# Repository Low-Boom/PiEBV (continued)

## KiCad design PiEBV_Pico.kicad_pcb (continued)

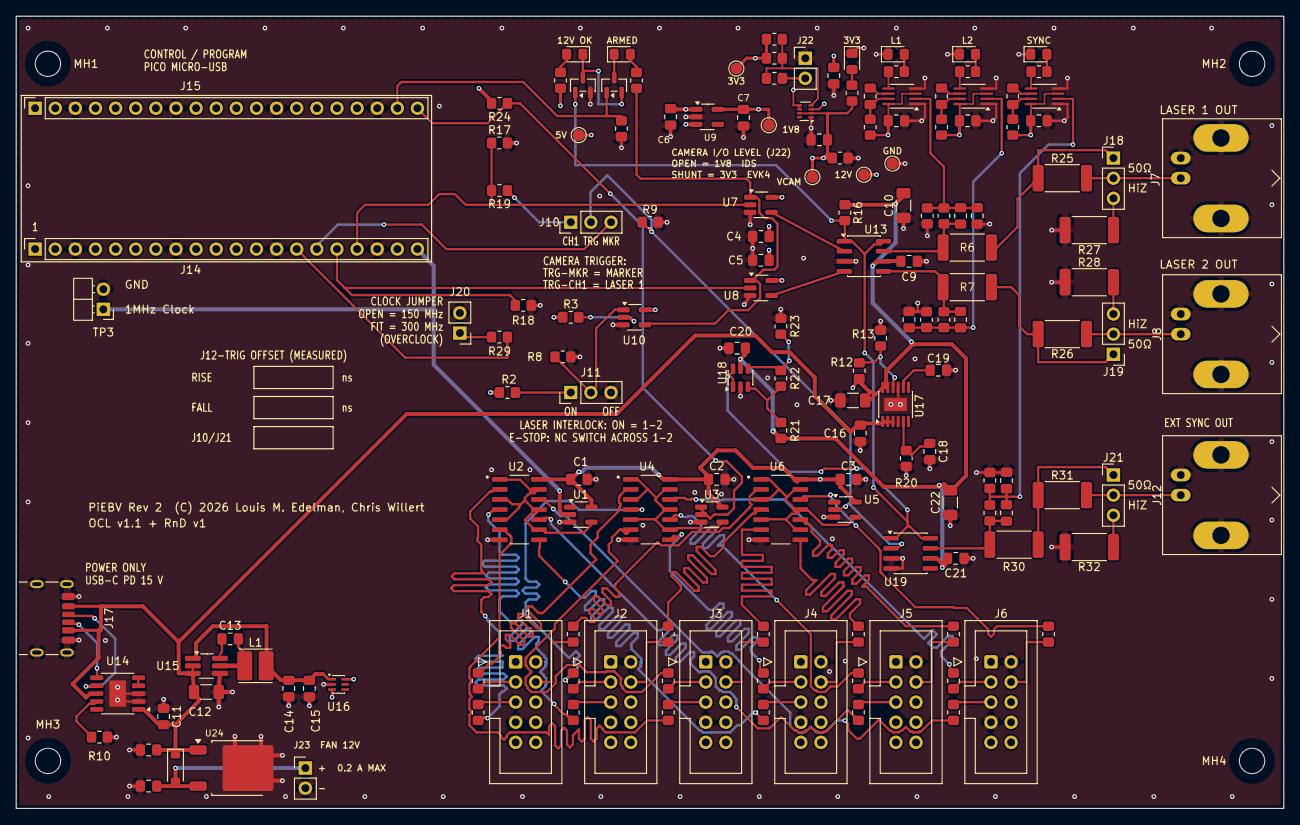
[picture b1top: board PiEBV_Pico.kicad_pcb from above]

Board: 4 copper layers, 160.0 x 100.0 mm, 164 parts (0 on the bottom side), 110 nets.

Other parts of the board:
MH1, MH2, MH3, MH4: MountingHole_3.2mm_M3

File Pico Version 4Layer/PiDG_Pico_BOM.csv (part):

"Reference","Value","Footprint","Qty","DNP","LCSC"
"C1-C5,C8,C9,C13,C20","0.1uF 50V X7R","Capacitor_SMD:C_0805_2012Metric_Pad1.18x1.45mm_HandSolder","9","","C49678"
"C6,C11,C16","1uF 50V X7R","Capacitor_SMD:C_0805_2012Metric_Pad1.18x1.45mm_HandSolder","3","","C28323"
"C7","2.2uF 16V X7R","Capacitor_SMD:C_0805_2012Metric_Pad1.18x1.45mm_HandSolder","1","","C28234"
"C10,C12,C17","10uF 50V X7R","Capacitor_SMD:C_1206_3216Metric_Pad1.33x1.80mm_HandSolder","3","","C89632"
"C14,C15","22uF 25V X5R","Capacitor_SMD:C_0805_2012Metric_Pad1.18x1.45mm_HandSolder","2","","C45783"
"C18","22nF 50V X7R","Capacitor_SMD:C_0805_2012Metric_Pad1.18x1.45mm_HandSolder","1","","C1729"
"C19","10nF 50V X7R","Capacitor_SMD:C_0805_2012Metric_Pad1.18x1.45mm_HandSolder","1","","C1710"
"L1","4.7uH, Isat >= 1.5 A","Inductor_SMD:L_Cenker_CKCS4030","1","","C354587"
"R2,R3,R5","3k3","Resistor_SMD:R_0805_2012Metric_Pad1.20x1.40mm_HandSolder","3","","C26010"
"R6,R7","68 1% 2W","Resistor_SMD:R_2512_6332Metric_Pad1.40x3.35mm_HandSolder","2","","C2793964"
"R25,R26","47 1% 2W (laser Hi-Z mode series)","Resistor_SMD:R_2512_6332Metric_Pad1.40x3.35mm_HandSolder","2","","C7209419"
"R27,R28","82 1% 2W (laser Hi-Z mode shunt)","Resistor_SMD:R_2512_6332Metric_Pad1.40x3.35mm_HandSolder","2","","C7468298"
"R8,R9,R17,R18,R24","10k","Resistor_SMD:R_0805_2012Metric_Pad1.20x1.40mm_HandSolder","5","","C17414"
"R10","56k","Resistor_SMD:R_0805_2012Metric_Pad1.20x1.40mm_HandSolder","1","","C17756"
"R12","100k 0.1%","Resistor_SMD:R_0805_2012Metric_Pad1.20x1.40mm_HandSolder","1","","C122537"
"R13","5.36k 0.1%","Resistor_SMD:R_0805_2012Metric_Pad1.20x1.40mm_HandSolder","1","","C706247"
"R16","100k","Resistor_SMD:R_0805_2012Metric_Pad1.20x1.40mm_HandSolder","1","","C149504"
"R19","100","Resistor_SMD:R_0805_2012Metric_Pad1.20x1.40mm_HandSolder","1","","C17408"
"R20","750 1%","Resistor_SMD:R_0805_2012Metric_Pad1.20x1.40mm_HandSolder","1","","C17818"
"R21","150k 1%","Resistor_SMD:R_0805_2012Metric_Pad1.20x1.40mm_HandSolder","1","","C17470"
"R22","1.2k 1%","Resistor_SMD:R_0805_2012Metric_Pad1.20x1.40mm_HandSolder","1","","C17379"
"R23","4.7k 1%","Resistor_SMD:R_0805_2012Metric_Pad1.20x1.40mm_HandSolder","1","","C17673"
"U1,U5","74LVC1G04","Package_TO_SOT_SMD:SOT-23-5_HandSoldering","2","","C7827"
"U3","74LVC1G00 (SN74LVC1G00DBVR, pixel-reset NAND)","Package_TO_SOT_SMD:SOT-23-5_HandSoldering","1","","C7826"
"U2,U4,U6","SN74LVC04AD","SN74LVC04AD:SOIC127P600X175-14N","3","","C485074"
"U7,U8,U10","74AHCT1G08","Package_TO_SOT_SMD:SOT-23-5_HandSoldering","3","","C113521"
"U9","NCP718xSN180","Package_TO_SOT_SMD:SOT-23-5_HandSoldering","1","","C892792"
"U12","74LVC1G17","Package_TO_SOT_SMD:SOT-23-5_HandSoldering","1","","C7836"
"U13","UCC27524","Package_SO:SOIC-8_3.9x4.9mm_P1.27mm","1","","C465729"
"U14","CH224A","Package_SO:SSOP-10-1EP_3.9x4.9mm_P1mm_EP2.1x3.3mm","1","","C42459160"
"U15","AP63205WU","Package_TO_SOT_SMD:TSOT-23-6_HandSoldering","1","","C2071056"
"U16","LM66100DCK","Package_TO_SOT_SMD:SOT-363_SC-70-6","1","","C2869734"
"U17","LT3065EDD#TRPBF (Analog Devices, adjustable)","Package_DFN_QFN:DFN-10-1EP_3x3mm_P0.5mm_EP1.65x2.38mm","1","","C670143"
"U18","TPS3700DDCR","Package_TO_SOT_SMD:SOT-23-6","1","","C33002"
"J1-J6","Conn_02x05_Odd_Even","Connector_IDC:IDC-Header_2x05_P2.54mm_Vertical","6","","C5665"
"J7,J8,J12","BNC 50R Kinghelm KH-BNC50-3511 (Laser 1 / Laser 2 / Pixel Reset)","PiDG_Local:BNC_Kinghelm_KH-BNC50-3511_Horizontal","3","","C2837587"
"J10,J11,J18,J19","Header 1x03 (J10 trigger select / J11 laser enable / J18, J19 laser output mode)","Connector_PinHeader_2.54mm:PinHeader_1x03_P2.54mm_Vertical","4","","C49257"
"(loose)","Jumper shunt, 2.54 mm 2-pin","-","4","Not placed on the board - fit J10 on 2-3, J11 on 1-2 (lasers enabled), J18 and J19 on 1-2 (50 ohm outputs) by hand","C100114"
"J16","Header 1x03 right-angle (EN/TRIG/GND)","PiDG_Local:PinHeader_1x03_P2.54mm_Horizontal_EdgeTrim","1","","C32713262"
"J17","USB-C receptacle 16P (HRO TYPE-C-31-M-12)","PiDG_Local:USB_C_Receptacle_HRO_TYPE-C-31-M-12_EdgeTrim","1","","C165948"
"TP3","Header 1x02 right-angle (1MHz sync + GND)","PiDG_Local:PinHeader_1x02_P2.54mm_Horizontal_EdgeTrim","1","","C32713261"
"TP4","Header 1x02 (CH2 monitor + GND)","Connector_PinHeader_2.54mm:PinHeader_1x02_P2.54mm_Vertical","1","","C32713268"
"J14,J15","Pico Socket A/B","Connector_PinSocket_2.54mm:PinSocket_1x20_P2.54mm_Vertical","2","","C2905423"
"U11","Raspberry Pi Pico 2 W","(no PCB footprint - plugs into J14/J15)","1","DNP - socket-mounted, do not place; source module separately",""
"MH1-MH4","M3 mounting hole","MountingHole:MountingHole_3.2mm_M3","4","Mechanical only - NPTH, nothing to place",""
"","","","","",""
"NOTE","U9 must be the FIXED 1.8 V NCP718 (NCP718xSN180, e.g. NCP718BSN180T1G or NCP718ASN180T1G)","Sets the camera I/O level. The IDS UE-39B0XCP-E I/O pins are 1.8 V sensor-level; do not substitute a 1.65 V, 1.7 V or 3.3 V option.","","",""
"NOTE","C6 is on +5V, C7 on +1V8 - use X7R, C6 rated >= 10 V","NCP718 needs >= 1 uF ceramic on its output for stability; C7 = 2.2 uF gives margin after DC-bias derating.","","",""
"NOTE","U12 must be a Schmitt-trigger part (74LVC1G17)","Gives the Pixel Reset BNC TTL-compatible thresholds and 0.5-0.8 V of hysteresis at 3.3 V. A plain 74LVC1G08/1G34 is not a substitute.","","",""
"NOTE","J16/TP3/J17 use PiDG_Local *_EdgeTrim footprint variants","Identical part and pad geometry to the stock footprints; only the silkscreen is clipped where the connector reaches the board edge. Order the standard parts.","","",""
"NOTE","R8 is a fail-safe interlock pull-down","Holds U10 pin 1 low when no jumper is fitted on J11, so the lasers default to DISABLED. R2 (3k3) still wins when the J11 1-2 jumper is fitted.","","",""
"NOTE","R9 is the J10 trigger-select pull-down","Holds PWM_TRIG_TAP (U5 input) low when no shunt is fitted on J10, so all six camera trigger lines idle low instead of floating.","","",""
"NOTE","U7/U8/U10 must be AHCT (TTL-input) parts, not LVC","At VCC = 5 V an LVC input needs 0.7 x VCC = 3.5 V to read high; the Pico drives these from 3.3 V GPIOs. AHCT reads high above 2.0 V.","","",""
"NOTE","R10 = 56k sets the USB PD request to 15 V","CH224A CFG1 table (datasheet Table 5-1): 6k8 = 9 V, 24k = 12 V, 56k = 15 V, 120k = 20 V, 210k = 28 V. Do not leave R10 off - an open CFG1 is outside the table. The laser outputs need a charger that offers 15 V (any USB-PD charger rated over 27 W).","","",""
"NOTE","U14 must be the CH224A (not the CH224K)","CH224A pin 1 (VHV) and pin 8 (VBUS) connect directly to VBUS_PD by copper, as the WCH CH224K-to-CH224A guide (datasheet 7.2.1) requires; R11/R15 of the CH224K design were removed. Do not fit a CH224K: it is discontinued, and its pin 1 is a 3.6 V VDD pin that VBUS_PD would destroy.","","",""
"NOTE","R12/R13 must be 0.1 % parts; R6/R7 1 %","They set the 11.8 V laser-driver rail and hence the LDP-V trigger amplitude (4.54-5.14 V into 50 ohm with U13 ROH 0-8.5 ohm, window 4.5-5.2 V). With 1 % divider resistors the worst-case corners fall outside the window.","","",""
"NOTE","U17 must be the ADJUSTABLE LT3065 (LT3065EDD), not a fixed LT3065-x","R12/R13 (100k/5.36k) set 11.8 V from the 600 mV ADJ reference. R20 (750 ohm) sets a 400 mA current limit and C18 (22 nF) on IMAX is required by the datasheet. Solder the exposed pad (two GND vias under it).","","",""
"NOTE","C9, C10, C17 see 12 V; C11, C12, C16 see up to 20 V","Use >= 25 V parts for C9/C10/C17 and >= 50 V for C11/C12/C16 (X7R). C12 is the only large cap on VBUS_PD (C11 and C16 are 1 uF each): keep total VBUS capacitance near the USB-C 10 uF sink limit.","","",""
"NOTE","U16 CE is tied to its VOUT (+5V)","That is TI's always-on reverse-blocking connection. With CE grounded the LM66100 does NOT block reverse current.","","",""
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
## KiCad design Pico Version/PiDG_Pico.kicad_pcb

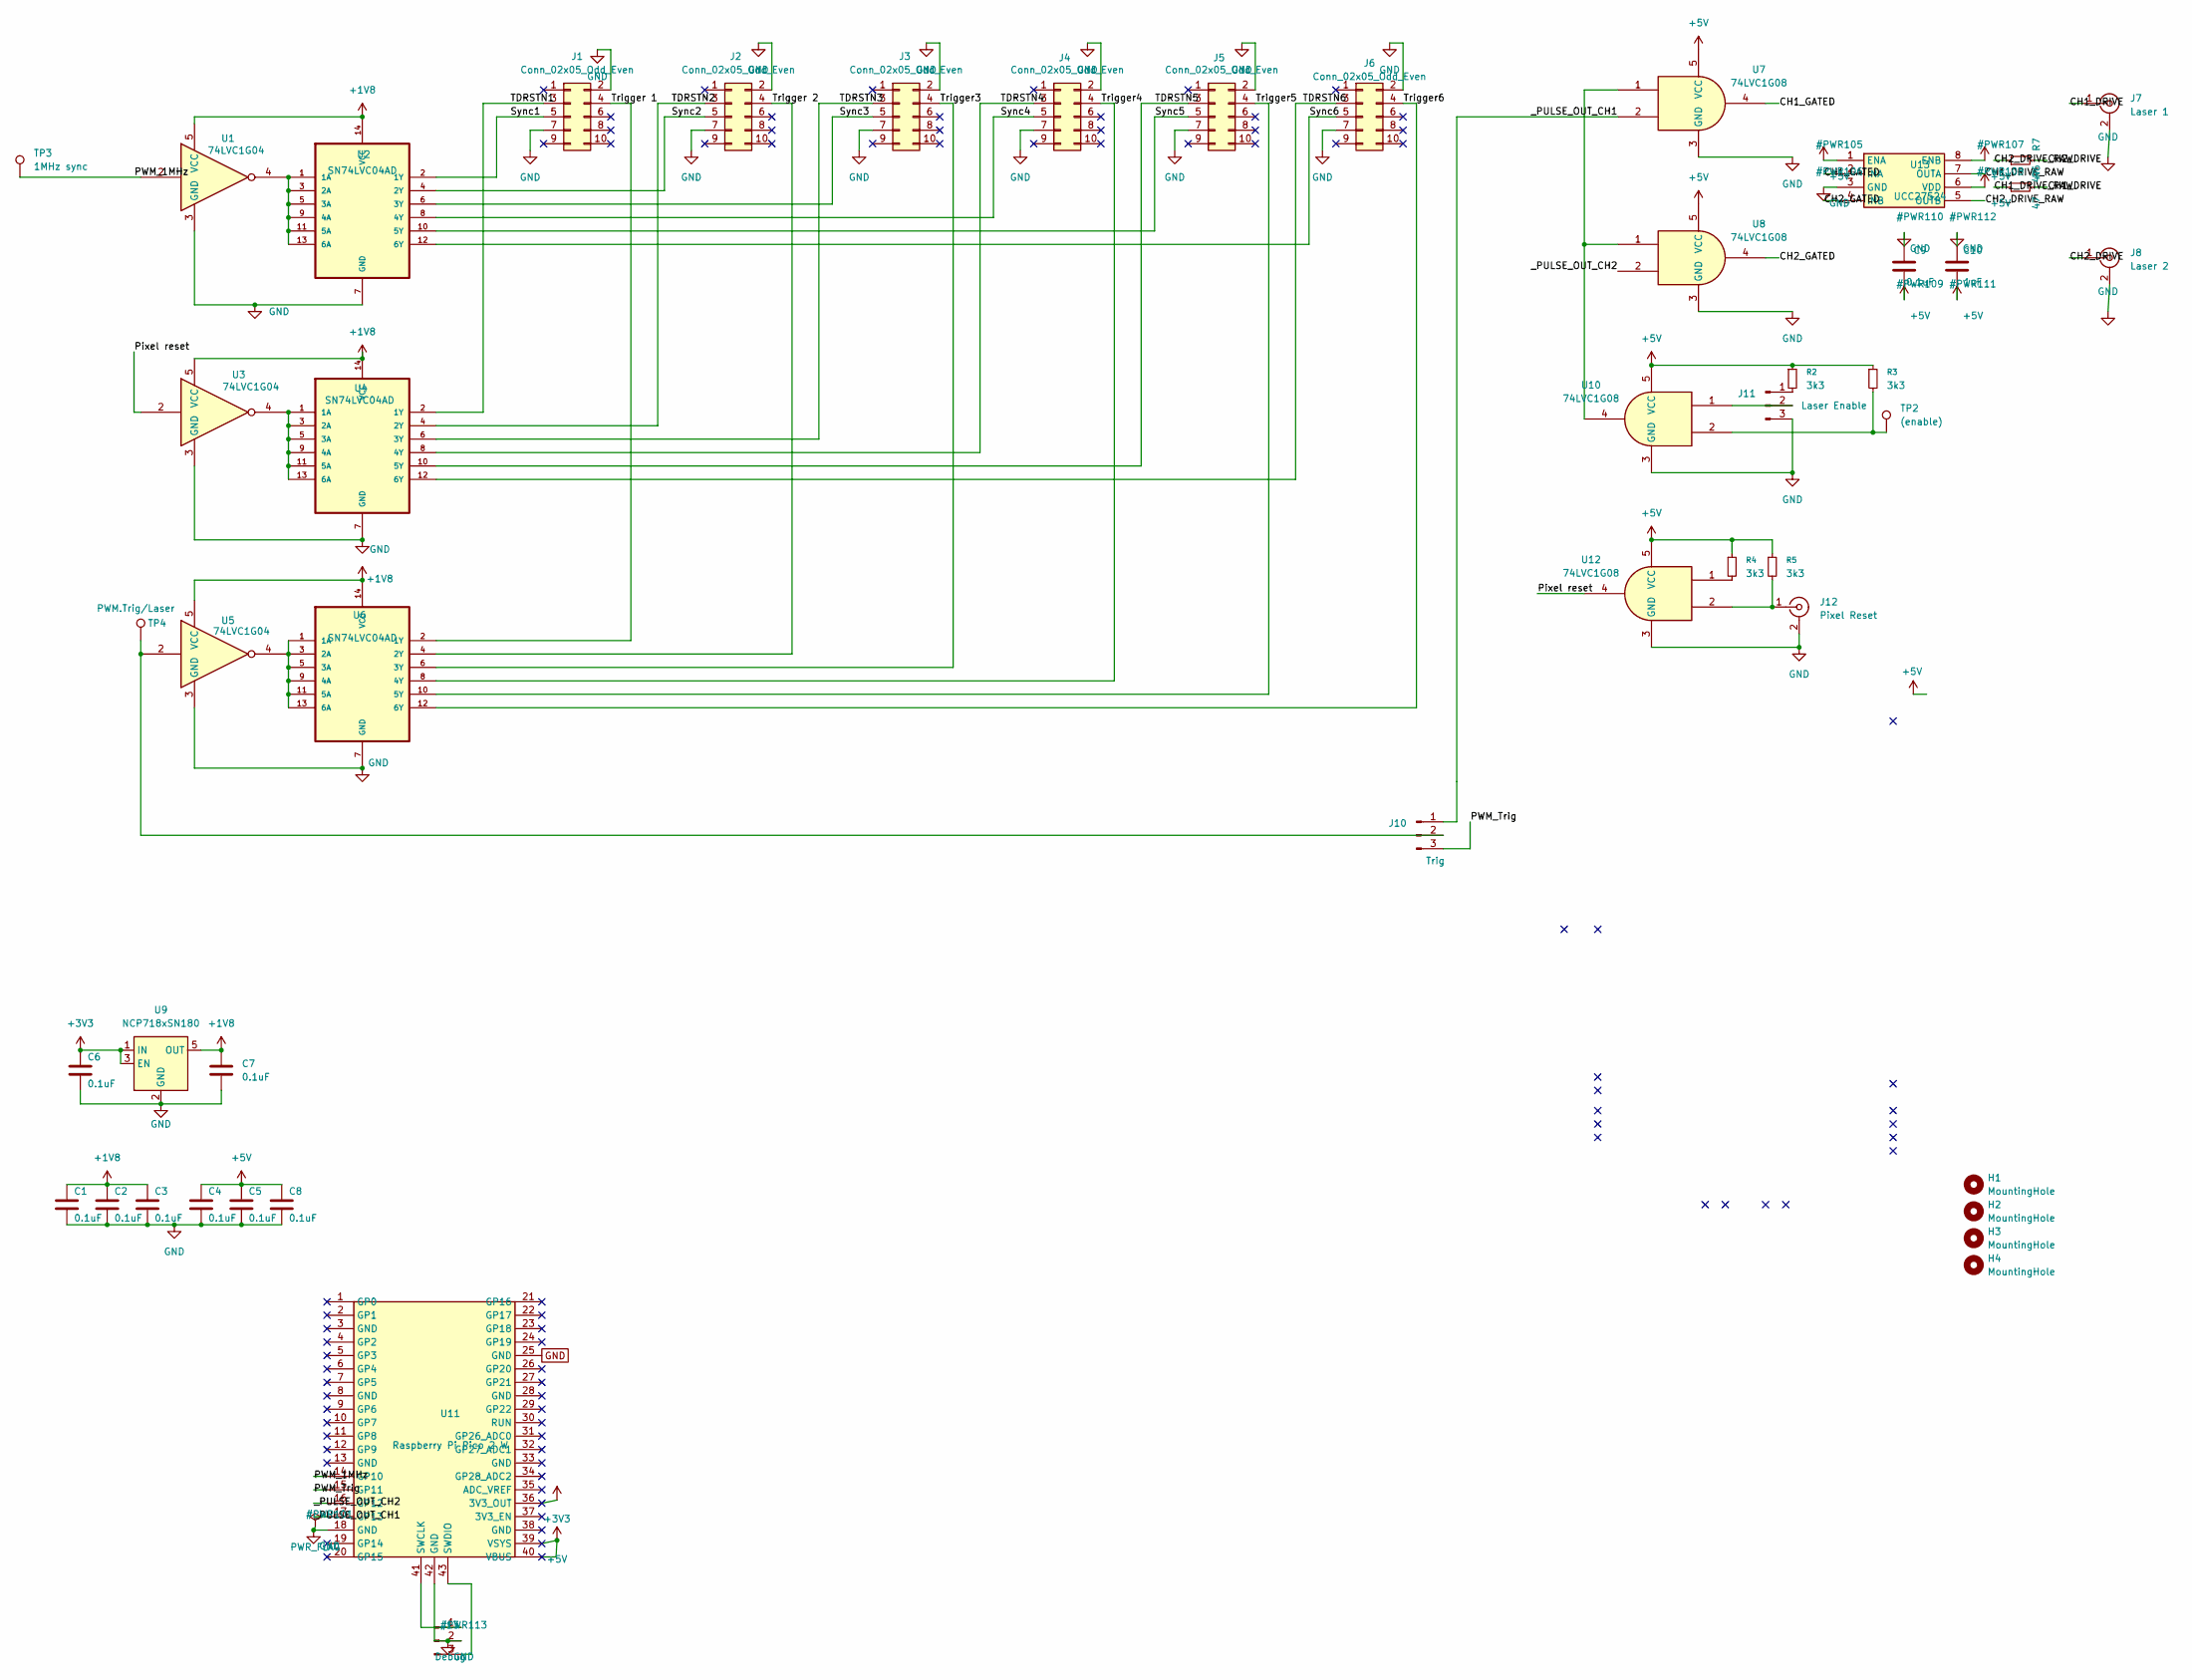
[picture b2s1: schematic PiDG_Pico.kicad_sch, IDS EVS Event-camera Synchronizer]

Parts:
C1, C2, C3, C4, C5, C6, C7, C8, C9: 0.1uF; C_0805_2012Metric_Pad1.18x1.45mm_HandSolder
C10: 1uF; C_0805_2012Metric_Pad1.18x1.45mm_HandSolder
H1, H2, H3, H4: MountingHole; MountingHole_3.2mm_M3_ISO14580
J1, J2, J3, J4, J5, J6: Conn_02x05_Odd_Even; IDC-Header_2x05_P2.54mm_Vertical
J7: Laser 1; BNC_Amphenol_B6252HB-NPP3G-50_Horizontal
J8: Laser 2; BNC_Amphenol_B6252HB-NPP3G-50_Horizontal
J10: Trig; PinHeader_1x03_P2.54mm_Vertical
J11: Laser Enable; PinHeader_1x03_P2.54mm_Vertical
J12: Pixel Reset; BNC_Amphenol_B6252HB-NPP3G-50_Horizontal
J13: Debug; PinHeader_1x03_P2.54mm_Vertical
R2, R3, R4, R5: 3k3; R_0805_2012Metric_Pad1.20x1.40mm_HandSolder
R6, R7: 47; R_0805_2012Metric_Pad1.20x1.40mm_HandSolder
TP2: (enable); PinHeader_1x01_P2.54mm_Horizontal
TP3: 1MHz sync; PinHeader_1x01_P2.54mm_Horizontal
TP4: PWM.Trig/Laser; PinHeader_1x01_P2.54mm_Horizontal
U1, U3, U5: 74LVC1G04; SOT-23-5_HandSoldering
U2, U4, U6: SN74LVC04AD; SOIC127P600X175-14N
U7, U8, U10, U12: 74LVC1G08; SOT-23-5_HandSoldering
U9: NCP718xSN180; SOT-23-5
U11: Raspberry Pi Pico 2 W; RPi_Pico2W_SMD_TH
U13: UCC27524; SOIC-8_3.9x4.9mm_P1.27mm

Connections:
+1V8: C1.1, C2.1, C3.1, C7.1, U1.5 (VCC), U2.14 (VCC), U3.5 (VCC), U4.14 (VCC), U5.5 (VCC), U6.14 (VCC), U9.5 (OUT)
+3V3: C6.1, U9.1 (IN), U9.3 (EN), U11.36 (3V3_OUT)
+5V: C4.1, C5.1, C8.1, C9.2, C10.2, R2.1, R3.1, R4.1, R5.1, U7.5 (VCC), U8.5 (VCC), U10.5 (VCC), U11.39 (VSYS), U11.40 (VBUS), U12.5 (VCC), U13.1 (ENA), U13.6 (VDD), U13.8 (ENB)
CH1_DRIVE: J7.1 (In), R6.2
CH1_DRIVE_RAW: R6.1, U13.7 (OUTA)
CH1_GATED: U7.4, U13.2 (INA)
CH2_DRIVE: J8.1 (In), R7.2
CH2_DRIVE_RAW: R7.1, U13.5 (OUTB)
CH2_GATED: U8.4, U13.4 (INB)
GND: C1.2, C2.2, C3.2, C4.2, C5.2, C6.2, C7.2, C8.2, C9.1, C10.1, J1.2, J1.7, J2.2, J2.7, J3.2, J3.7, J4.2, J4.7, J5.2, J5.7, J6.2, J6.7, J7.2 (Ext), J8.2 (Ext), J11.3, J12.2 (Ext), J13.2, U1.3 (GND), U2.7 (GND), U3.3 (GND), U4.7 (GND), U5.3 (GND), U6.7 (GND), U7.3 (GND), U8.3 (GND), U9.2 (GND), U10.3 (GND), U11.18 (GND), U11.25 (GND), U11.42 (GND), U12.3 (GND), U13.3 (GND)
unnamed: J1.3, U4.2 (1Y)
unnamed: J1.5, U2.2 (1Y)
unnamed: J2.3, U4.4 (2Y)
unnamed: J2.5, U2.4 (2Y)
unnamed: J3.3, U4.6 (3Y)
unnamed: J3.5, U2.6 (3Y)
unnamed: J4.3, U4.8 (4Y)
unnamed: J4.5, U2.8 (4Y)
unnamed: J5.3, U4.10 (5Y)
unnamed: J6.3, U4.12 (6Y)
unnamed: J10.2, TP4.1, U5.2
unnamed: J11.2, U10.1
unnamed: J11.1, R2.2
unnamed: J12.1 (In), R5.2, U12.2
unnamed: J13.1, U11.41 (SWCLK)
unnamed: J13.3, U11.43 (SWDIO)
unnamed 27: R3.2, TP2.1, U10.2; also elsewhere on the board
unnamed: R4.2, U12.1
unnamed: U1.4, U2.1 (1A), U2.3 (2A), U2.5 (3A), U2.9 (4A), U2.11 (5A), U2.13 (6A)
unnamed: U3.4, U4.1 (1A), U4.3 (2A), U4.5 (3A), U4.9 (4A), U4.11 (5A), U4.13 (6A)
unnamed: U5.4, U6.1 (1A), U6.3 (2A), U6.5 (3A), U6.9 (4A), U6.11 (5A), U6.13 (6A)
unnamed: U7.1, U8.1, U10.4
PWM_Trig: J10.3, U11.15 (GP11)
Pixel reset: U3.2, U12.4
Sync5: J5.5, U2.10 (5Y)
Sync6: J6.5, U2.12 (6Y)
Trigger3: J3.4, U6.6 (3Y)
Trigger4: J4.4, U6.8 (4Y)
Trigger5: J5.4, U6.10 (5Y)
Trigger6: J6.4, U6.12 (6Y)
Trigger 1: J1.4, U6.2 (1Y)
Trigger 2: J2.4, U6.4 (2Y)
_PULSE_OUT_CH1: J10.1, U7.2, U11.17 (GP13)
_PULSE_OUT_CH2: U8.2, U11.16 (GP12)

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
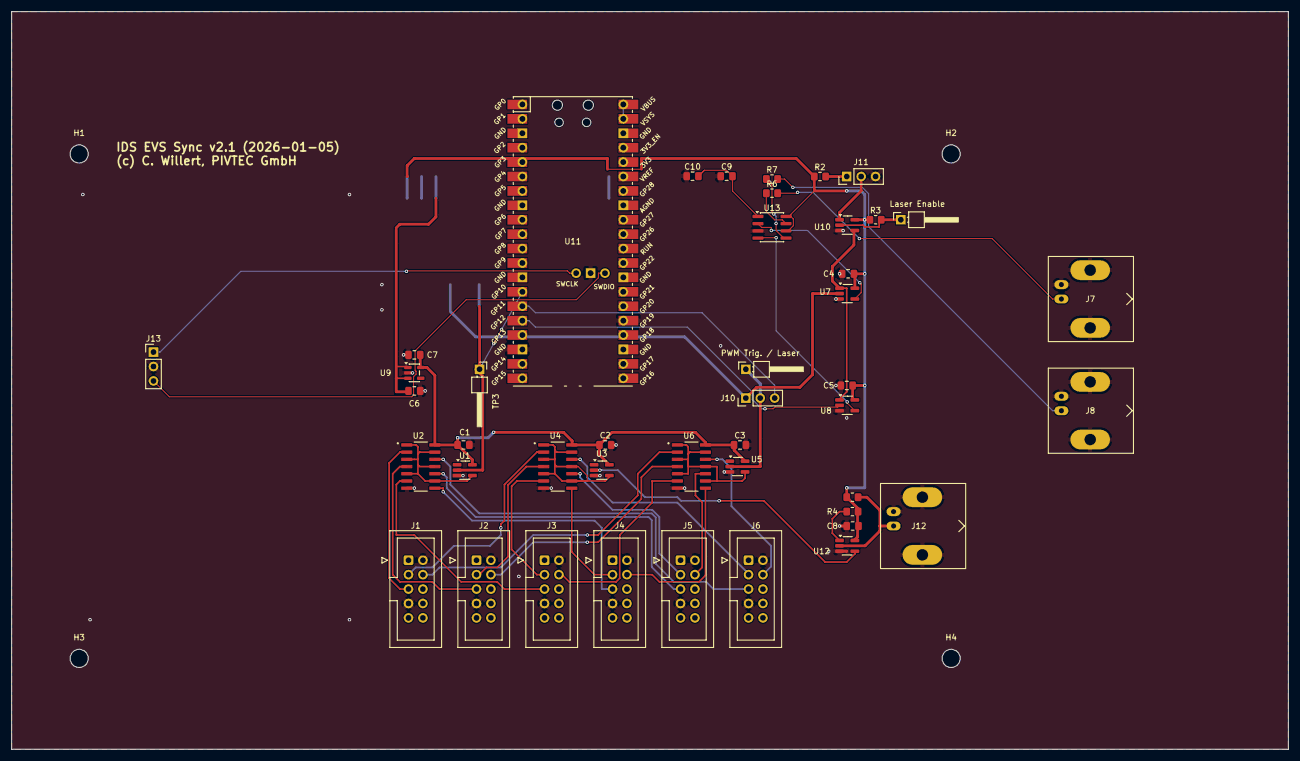
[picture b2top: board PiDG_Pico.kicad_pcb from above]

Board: 2 copper layers, 225.0 x 130.0 mm, 48 parts (0 on the bottom side), 45 nets.

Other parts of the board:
Laser Enable: (enable); PinHeader_1x01_P2.54mm_Horizontal
PWM Trig. / Laser: PWM.Trig/Laser; PinHeader_1x01_P2.54mm_Horizontal

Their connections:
unnamed 27: Laser Enable.1; also elsewhere on the board

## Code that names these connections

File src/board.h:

#pragma once
// GPIO assignments of the PiEBV 4-layer board. These MUST match
// "PiEBV_Pico.kicad_sch" (repo root). The Pico plugs into sockets
// J14/J15; J14 pad n = Pico physical pin n.
//
//   constant     GPIO   Pico pin   J14 pad   board net         drives
//   ----------   ----   --------   -------   ---------------   ---------------------------------
//   kPinMarker   GP11      15         15     PWM_Trig          J10.3 -> U5 -> U6 -> Trigger1..6, and
//                                                                U19 -> J12 (External Sync Out)
//   kPinCh2      GP12      16         16     _PULSE_OUT_CH2    U8 -> U13 -> J8 (Laser 2); R18 10k to GND
//   kPinCh1      GP13      17         17     _PULSE_OUT_CH1    U7 -> U13 -> J7 (Laser 1); R17 10k to GND
//   kPinSync     GP15      20         20     PWM_1MHz          U1 -> U2 -> Sync1..6, TP3. clk_gpout1, not PIO:
//                                                                only GP13/15/21 (23-25 internal) have a clock
//                                                                output, and GP13 is CH1 (sync_clock.h).
//   kPinPixGate  GP16      21    J15 pad 20 PIXRST_GATE       U3 pins 1+2 (NAND as inverter) -> U4 ->
//                                                                TDRSTN1..6; R24 10k to +3V3. Driven INVERTED
//                                                                (main.cpp): PIO latch high = pixels in reset.
//   kPinClockSel GP10      14         14     CLK_SEL           R29 1k -> J20.1 (J20.2 = GND). Clock jumper, read once
//                                                                at boot (clock_mode.cpp): fitted = 300 MHz, open = 150 MHz.
//                                                                Internal pull-up only; no capacitor on the net. R29
//                                                                limits the current if GP10 is driven with the shunt fitted.
//   kPinArmedLed GP17      22    J15 pad 19 ARMED_LED         Q2 gate (R38 100k to GND) -> D3 "ARMED" (Rev 2 board). HIGH while
//                                                                ARMED. D3 lights only if J11 is closed and +12 V is good as
//                                                                well (LASER_EN -> D3 -> Q2 -> Q1). Status only: it gates nothing.
//
// CH1 is the HIGHER GPIO and CH2 the lower. The order is deliberate, so do not
// "tidy" these into ascending order.
// GP2-GP5 are not connected on this board. GP17 is not connected on the Rev 1 board (driving it there is harmless). GP10 (SYNC before it moved to the clock generator)
// is now the clock jumper input.

constexpr unsigned kPinMarker = 11;
constexpr unsigned kPinCh2 = 12;
constexpr unsigned kPinCh1 = 13;
constexpr unsigned kPinSync = 15;
constexpr unsigned kPinPixGate = 16;
constexpr unsigned kPinClockSel = 10;
constexpr unsigned kPinArmedLed = 17;

constexpr unsigned kLaserPinMask = (1u << kPinCh1) | (1u << kPinCh2);
